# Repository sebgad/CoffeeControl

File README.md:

# CoffeeControl :coffee:

This is primarily a temperatur controller for a Rancilio Silvia Espresso machine. Parameters for controller and running the controller can be configured over a web interface. 

**default settings / no connection to wifi possible:** If no wifi is available to connect, a soft-AP (SSID: 'SilviaCoffeeCtrl', no PW)  is setup to control. It can be accessed either by the IP address of the controller or the domain http://coffee.local. In this mode plotting is currently not working (because googleCharts is used). Over the page "settings" the SSID and Password can be setup.

The project is based on an esp32 via the arduino IDE.

## code

### required aduino libaries:
- for Json handling [ArduinoJson](https://arduinojson.org/)
- for Webserver [ESPAsyncWebserver](https://github.com/me-no-dev/ESPAsyncWebServer)
- for Async TCP transfer [AsyncTCP](https://github.com/me-no-dev/AsyncTCP)

In addition there is one file required for individual setup:

"Pt1000.h" for defining individual characteristic of wheatstone bridge:
```c++
#ifndef Pt1000_h
#define Pt1000_h

#define Pt1000_CONV_SQUARE  // define for square interpolation

#include "Arduino.h"

// Define coefficients for linear regression function
// use #define Pt1000_CONV_LINEAR if you want to use the linear interpolation
// variable are only requred if this define is set
const float fPt1000LinCoeffX1 = 433.6520668;
const float fPt1000LinCoeffX0 = 82.01975366;

// Define coefficients for quadratic regression function
// use #define Pt1000_CONV_SQUARE if you want to use the square interpolation
// variable are only requred if this define is set
const float fPt1000SquareCoeffX2 = 295.16714369;
const float fPt1000SquareCoeffX1 = 417.84868016;
const float fPt1000SquareCoeffX0 = 76.91861221;

// Define lookup table for temperature calculation
// use #define Pt1000_CONV_LOOK_UP_TABLE if you want to use the lookup table
// variable are only requred if this define is set
const float arrPt1000LookUpTbl[][2] = {
                                        {-0.21396866840731069, 0.0},
                                        {-0.19826086393703643, 5.0},
                                        {-0.18283911631429636, 10.0},
                                        {-0.16770344877338753, 15.0},
                                        {-0.15282330361877822, 20.0},
                                        {-0.13821466591521075, 25.0},
                                        {-0.12386291635089636, 30.0},
                                        {-0.10976138828633408, 35.0},
                                        {-0.09589652769003139, 40.0},
                                        {-0.08227645893153232, 45.0},
                                        {-0.06888104591949339, 50.0},
                                        {-0.05571158923387528, 55.0},
                                        {-0.0427624663099406, 60.0},
                                        {-0.0300282397238783, 65.0},
                                        {-0.017503649635036495, 70.0},
                                        {-0.00518360659538545, 75.0},
                                        {0.0069431178724726535, 80.0},
                                        {0.01886859632220499, 85.0},
                                        {0.03060996495366849, 90.0},
                                        {0.04216540043842523, 95.0},
                                        {0.05353924250669009, 100.0},
                                        {0.06472982975573649, 105.0},
                                        {0.07575883980844787, 110.0},
                                        {0.08661262418699037, 115.0},
                                        {0.09730088303101485, 120.0},
                                        {0.10782733455505109, 125.0},
                                        {0.11820106425587913, 130.0},
                                        {0.12841994955774214, 135.0},
                                        {0.13848205967873975, 140.0},
                                        {0.1484014359031887, 145.0},
                                        {0.15817588158467566, 150.0},
                                        {0.16780851306788105, 155.0},
                                        {0.17730235788402426, 160.0},
                                        {0.18666535708795248, 165.0},
                                        {0.19589030865119572, 170.0},
                                        {0.20498993006709912, 175.0},
                                        {0.21395711383340363, 180.0},
                                        {0.22280417956398454, 185.0},
                                        {0.23152881217857227, 190.0},
                                        {0.2401335018563869, 195.0},
                                        {0.24862067160467974, 200.0}
                                      };
#endif
```

## PCB
- The PCB was created via KiCAD [KiCAD](https://www.kicad.org/)
- Rouing was done via the autorouter from freerouting [freerouting](https://github.com/freerouting/freerouting)
- The sorce fiels of the PCB are in *tools/PCB-KiCAD/EspressoV1*
Note:
- The autorouter cannot create a 100% working PCB but is a good start 
- Do not sace the preferenences of the outorouter. Otherweise the routing cannot be redone. See [here](https://github.com/freerouting/freerouting/issues/26#issuecomment-814837891)
- The Design uses an own libary. KiCAD might not be able to find the file initially. 
	- re-Open KiCAD: Do Fixes in "Symbol Editor" and "Footprint Editor":
	- Preferences -> Symbol Libaries|Manage Footprint Libaries : update the path of the esp32 libary
	- close and open KiCAD

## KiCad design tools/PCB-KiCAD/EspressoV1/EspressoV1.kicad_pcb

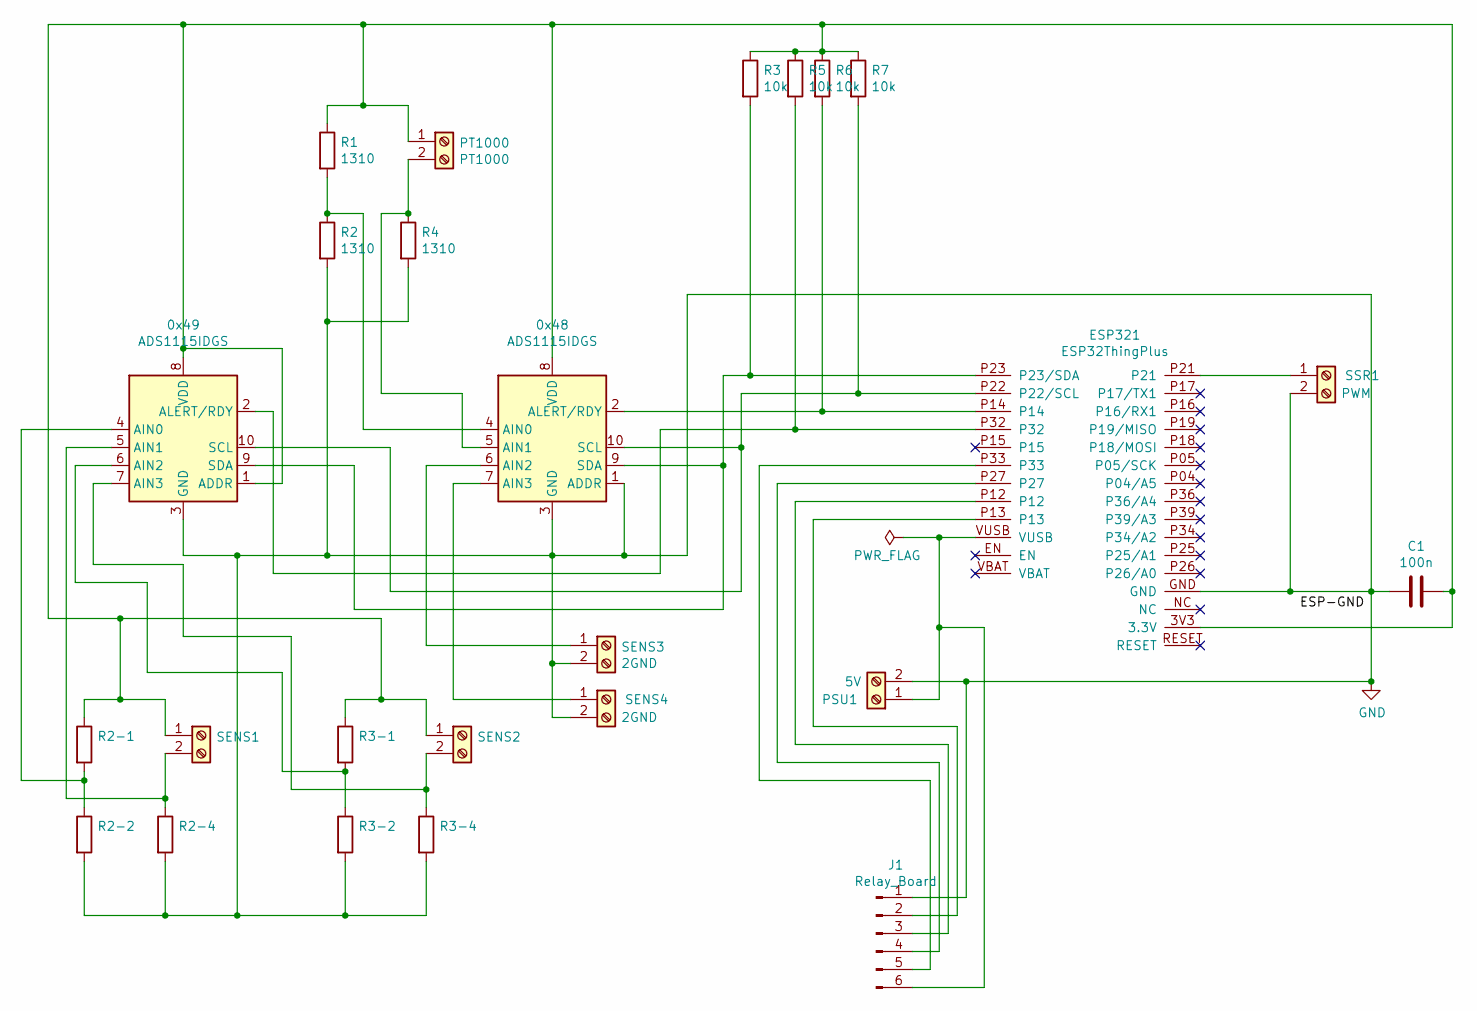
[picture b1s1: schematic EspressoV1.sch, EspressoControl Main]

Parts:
0x48, 0x49: ADS1115IDGS; ADS1115
C1: 100n; C_Rect_L13.0mm_W5.0mm_P10.00mm_FKS3_FKP3_MKS4
ESP321: ESP32ThingPlus
J1: Relay_Board; PinHeader_1x06_P2.54mm_Vertical
PSU1: 5V; TerminalBlock_Phoenix_MKDS-1,5-2-5.08_1x02_P5.08mm_Horizont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
PT1000: PT1000; TerminalBlock_Phoenix_MKDS-1,5-2-5.08_1x02_P5.08mm_Horizont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
R1, R2, R3-1, R3-2, R3-4, R4: 1310; R_Axial_DIN0207_L6.3mm_D2.5mm_P10.16mm_Horizontal
R2-1, R2-2, R2-4: 0; R_Axial_DIN0207_L6.3mm_D2.5mm_P10.16mm_Horizontal
R3, R5, R6, R7: 10k; R_Axial_DIN0207_L6.3mm_D2.5mm_P10.16mm_Horizontal
SENS1: -; TerminalBlock_Phoenix_MKDS-1,5-2-5.08_1x02_P5.08mm_Horizont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
SENS2: PT1000; TerminalBlock_Phoenix_MKDS-1,5-2-5.08_1x02_P5.08mm_Horizont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
SENS3, SENS4: 2GND; TerminalBlock_Phoenix_MKDS-1,5-2-5.08_1x02_P5.08mm_Horizont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
SSR1: PWM; TerminalBlock_Phoenix_MKDS-1,5-2-5.08_1x02_P5.08mm_Horizont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

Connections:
GND: 0x48.1 (ADDR), 0x48.3 (GND), 0x49.3 (GND), C1.2, ESP321.GND, J1.1, PSU1.2, R2.2, R2-2.2, R2-4.2, R3-2.2, R3-4.2, R4.2, SENS3.2, SENS4.2, SSR1.2
unnamed: 0x48.2 (ALERT/RDY), ESP321.P14, R6.2
unnamed: 0x48.4 (AIN0), R1.2, R2.1
unnamed: 0x48.5 (AIN1), PT1000.2, R4.1
unnamed: 0x48.6 (AIN2), SENS3.1
unnamed: 0x48.7 (AIN3), SENS4.1
unnamed: 0x48.8 (VDD), 0x49.1 (ADDR), 0x49.8 (VDD), C1.1, ESP321.3V3 (3.3V), PT1000.1, R1.1, R2-1.1, R3.1, R3-1.1, R5.1, R6.1, R7.1, SENS1.1, SENS2.1
unnamed: 0x48.9 (SDA), 0x49.9 (SDA), ESP321.P23 (P23/SDA), R3.2
unnamed: 0x48.10 (SCL), 0x49.10 (SCL), ESP321.P22 (P22/SCL), R7.2
unnamed: 0x49.2 (ALERT/RDY), ESP321.P32, R5.2
unnamed: 0x49.4 (AIN0), R2-1.2, R2-2.1
unnamed: 0x49.5 (AIN1), R2-4.1, SENS1.2
unnamed: 0x49.6 (AIN2), R3-1.2, R3-2.1
unnamed: 0x49.7 (AIN3), R3-4.1, SENS2.2
unnamed: ESP321.P12, J1.3
unnamed: ESP321.P13, J1.2
unnamed: ESP321.P21, SSR1.1
unnamed: ESP321.P27, J1.4
unnamed: ESP321.P33, J1.5
unnamed: ESP321.VUSB, J1.6, PSU1.1

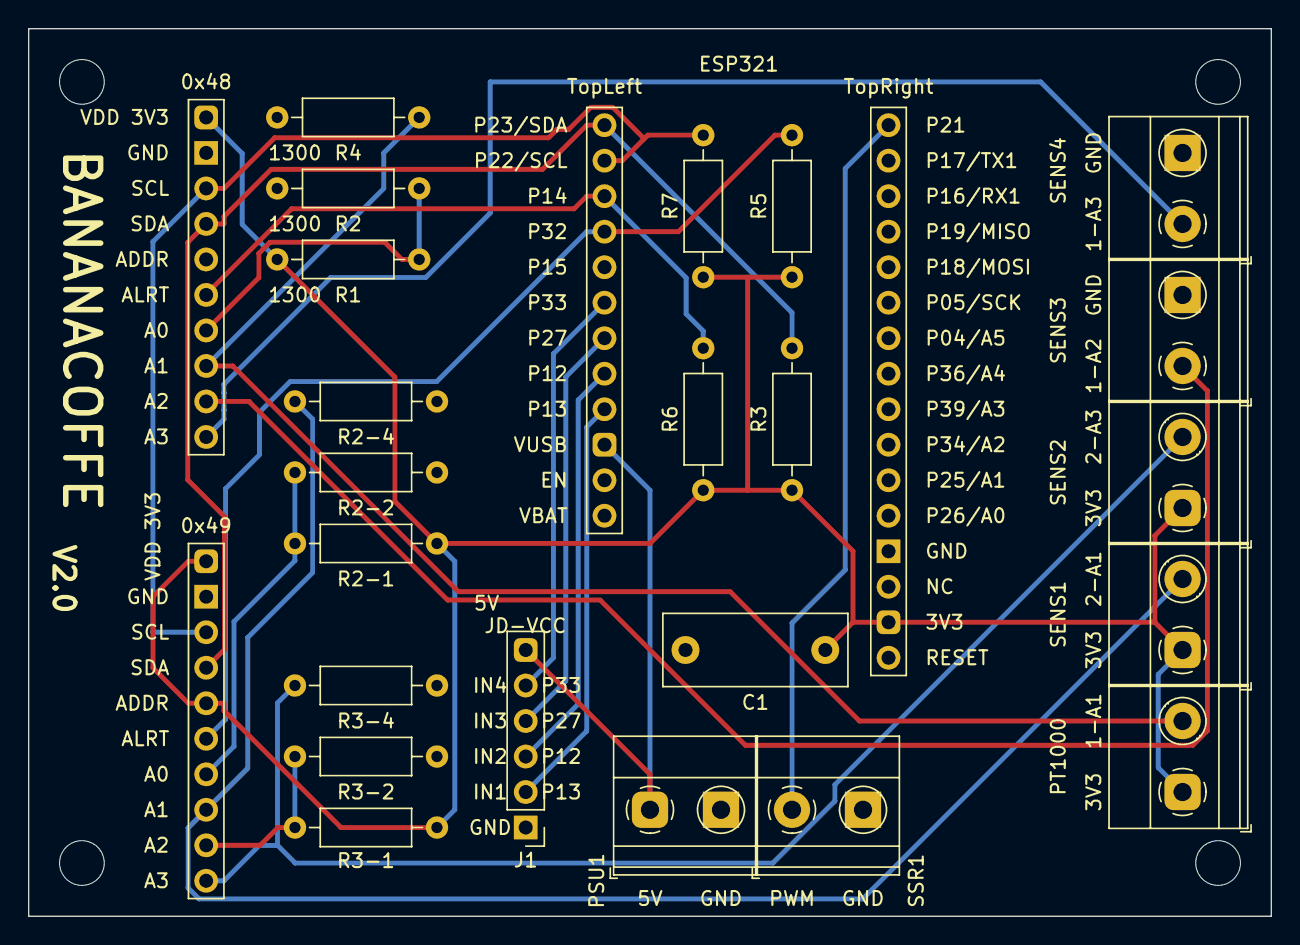
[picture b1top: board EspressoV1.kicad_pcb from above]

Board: 2 copper layers, 88.9 x 63.5 mm, 29 parts (0 on the bottom side), 20 nets.

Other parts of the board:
OL: MountingHole_3.2mm_M3
OR: MountingHole_3.2mm_M3
UL: MountingHole_3.2mm_M3
UR: MountingHole_3.2mm_M3

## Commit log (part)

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2021-04-24 inital create
2021-04-24 add .vscode to gitignore
2021-04-25 add wifi connection function
2021-04-25 add mDNS service
2021-04-25 Delete index.html
    delete because license is unknown
2021-04-25 add TODOs
2021-04-29 add timer and ISR based on https://techtutorialsx.com/2017/10/07/esp32-arduino-timer-interrupts/
2021-05-02 add index.html
2021-05-02 change layout of index.html
2021-05-08 divide stylesheet and java script for status table. add google graph
2021-05-08 start Json data handling
2021-05-09 add TODOs, have fun :-)
2021-05-12 Dont look at me. This is just an ugly debugg nano sketch for testing the SSR. This code is verry ugly.
2021-05-13 used pin 6 as slow "pwm"like and pin 3 as normal pwm
2021-05-13 naming mistake
2021-05-13 added shortcut to gitignore so i dont stage by mistake
2021-05-13 correct pwm usage
2021-05-15 add JSON generator, dummy output for debugging
2021-05-16 Add python file to calculate maximum signal measurement
2021-05-17 start implementing csv file
2021-05-22 add three timers, still bugfixing timer 3 (measurement stream)
2021-05-22 fixed timer3 issue
2021-05-24 sensor read out, pid control and measurement write depend now on one timer
2021-05-30 change timer settings, implement status variables, minor changes on setup
2021-05-30 added description to the readme
2021-05-30 start implementing ADS1115
2021-05-31 extend function getPolarity() and setPolarity()
2021-05-31 link fix for README.md
2021-05-31 added link and setup for online tool to simulate wheatstone bridge
2021-06-02 change bit shifting functionality and add missing register settings
2021-06-03 implement pinready mode
2021-06-03 add missing functionalities, add comments
2021-06-04 change bit significance conversion and add initial setup of ADS1115
2021-06-04 add physical conversion method
2021-06-10 setup temp sensor
2021-06-12 initial iteration of PCB. PCB created with KiCAD.
2021-06-12 added info about the PCB
2021-06-13 PT1000 lookup table; with 7 support points
2021-06-14 add physical conversion table, fix integer problem
2021-06-14 bugfix i2c func
2021-06-15 fix bitread and write in ADS1115 lib
2021-06-16 fix bitwrite()
2021-06-17 fix issue in writeBit and rename function
2021-06-18 change implementation from set- and read_physical in ADS1115 lib
2021-06-19 adapt calculation for Resistor R1,R2,R4 from 1310Ohm to 1298Ohm
2021-06-20 implement csv parsing in webserver to read out actual sensor values
2021-06-20 added PID and some comments
2021-06-21 added 1310 ohm calibration; fixt Pin typo
2021-06-21 1310 ohm setup
2021-06-26 change time column in measurement file
2021-06-26 define PT1000 conversion table in separate header file
2021-06-26 implement regression square function for readPhysical()
2021-06-26 get interpolation values for .h file
2021-06-26 read voltage in V
2021-06-27 adapt physical conversion set
2021-06-29 connect line chart with data.csv
2021-06-29 change pwm chart
2021-07-11 comment graphs.html, add another status indicator, but not finished
2021-07-14 cleanup main script, change register readout functionality in ADS1115 and change layout of graphs.html including css file
2021-08-21 minor changes
2021-08-27 add pid parameter handling
2021-08-27 implement ArduinoJson for parameter handling
2021-09-01 add JsonLib
2021-09-06 add comments
2021-09-10 adapted PID lib: fixed controller calculation; other coefficients; added OnOffThresholds
2021-09-10 implement parameter update
2021-09-10 clean up graphs.html
2021-09-11 finished Parameter setup
2021-09-12 extend online calibrations and functionality to up and download file
2021-09-12 added method to only add off or on threshold + spelling
2021-09-14 split setup function, bugfix graphs.html
2021-09-18 only use On threshold
2021-09-18 fist commissioning of temp controller. tuning parameters need to be adapted.
2021-09-18 updated tuning parameters
2021-09-20 added TODO so I dont forget
2021-09-26 add access protection for parameter file and measfile
2021-10-03 clean up web interface, add memory allocation to measurement file
2021-10-03 PCB V2
2021-10-03 correct resistor value
2021-10-10 add wifi signal strength information
2021-10-29 add softAP if wifi connection is not possible. Wifi settings now stored in json-file
2021-10-29 update wifi soft ap description
2021-11-01 remove include to WifiAccess.h file, bugfixes
2021-11-01 implement reconnect event on disconnect from wifi
2021-12-23 change pid controler, add ota functionality
2021-12-23 change coefficient names of PID controller, implement time factor switch for coefficients
2021-12-27 add raw measurement data
2021-12-28 clarify controller parameters
2021-12-28 added RGB LED for pin 13, 12 and 27 and on off pid
2021-12-29 LED write call every 2.5s for debouncing. Change orange to purple
2021-12-30 add json request lastValues, update index.html and graphs.html
2021-12-30 wifi SSID/PW is not default gotten from h-file
2021-12-30 add antiwindup, add control parameter ods file
2021-12-31 increase sensitivity of ADS1115 to +-0.256V, minor changes
2022-01-01 add conversion monitoring if sensor values are freezing, minor changes
2022-01-01 bugfix sensor diagnosis
2022-01-01 temporary disable diagnosis function. Need to analyze bug.
2022-01-03 remove diagnosis for now, because sum up the delta is not sufficient for identifying malfunction of ADS1115
2022-01-04 default python script; added to git ignore
2022-01-04 got orange and yellow working
    changes HW ins of Gereen and blue
2022-01-04 added tool to calc md5 for win10
2022-01-04 tool can now correctly been rerun
2022-01-04 added missing config parameters and made them changeable
2022-01-04 start reorganizing JSON, add menu.js for generating navbar
2022-01-05 add json structure and start changing http server
2022-01-06 change JSON structure and settings, remove channels from settings, led color change
2022-01-07 added 8-point mean filter option in getVoltVal
    default is no filter (off)
    filter is off
2022-01-07 implement signal filter, changed setup call order, minor fixes in pyhton scripts
2022-01-07 optimize settings.html page
2022-01-08 add savitzgy golay filter
2022-01-14 remove variable buffer size, add savitzky golay filter for odd buffer size
2022-01-15 change settings button layout
2022-01-16 adapt RGB LED brightness
2022-01-16 activating filter; but stopping implementation for now
2022-01-16 measurement of step response and py file to plot
2022-01-16 added diagnosis for when the sensor is stuck and had 10 times the same value
2022-01-16 adapt LED setColor()
2022-01-16 bugfix error LED status
2022-01-19 bugfix diagnosis function
2022-01-19 bugfix LED issue
2022-01-21 implement hardware watchdog functionality
2022-01-22 rework of diagnosis; not use min==max anymore but check for changed values
    rename of misleading variable name
2022-01-22 bugfix initializing buffer in ADS1115.cpp, updating all *.html, minor bugfixes, optimize webserver
2022-01-22 bugfix merge conflict :-)
2022-01-22 add gain factor for each color, e.g. orange, purple, etc.
2022-01-22 bugfix esp restart request over webserver, adapt JSON document size
2022-01-23 added favicon and renamed to BananaCoffee
2022-01-23 redirect fix when uploading files
2022-01-23 added missing import -> merge error fix
2022-01-23 temporary bugfix interrrupt call
2022-01-24 bugfix filter settings, setting filter size to 11, comment fileblock method to check repsonsiveness of webserver
2022-01-29 add ADS1015, state change state machine to implement oversampling in onAlertRdy()
2022-01-30 change to core v2 and littleFS
2022-01-30 bugfix
2022-02-04 change i2c in ads1015
2022-02-05 bugfix ADS1015 assignment
2022-02-06 fix i2c timing issue
2022-02-07 add ota.h and failsafe request
2022-02-08 change to ADS1115
2022-02-08 change filter size
2022-02-08 added favicons for littleFS
2022-02-13 combine all csv to one combined csv
2022-02-13 model for simulating step response
2022-02-19 add curve fit pyhton file
2022-02-27 show WiFi strength in index.html; better filtering and filter debugging.
2022-02-27 bugfix buffer print, change readOut WifiSignal
2022-03-03 cleanup and read the register without changing the filter buffer at the end of setup()
2022-03-05 change index.html layout
2022-03-05 fix first conversion
2022-03-15 start redirecting log output to logfile, add conversion mode diagnosis
2022-03-16 implement log rotation, add log.html to watch debug log
2022-03-16 bugfix diagnosis loop ESP_OK
2022-03-27 increase watchdog timeout, to cover time at reset. turn led to purple when ADS needs to be reconfigured
2022-12-26 add standby timeout
2023-06-04 fixed missing semicolon
2023-06-04 change timeout in i2c, operating range
2023-06-04 set default timeout to 1h
2023-06-08 removed false -positive detection of frozen value for temperatures below 35°C
2023-06-11 added log to timeout, high threshold and updated default values
2023-06-24 bugfix LED-Ctrl, extend timeout in I2C communication
2023-06-24 add wifi-reconnect() and remove wifi.connect() in mainloop
2023-06-24 bugfix iState check
2023-06-24 add wifi reconnect, change i2c clock speed, bugfix diagnosis
2023-09-19 disable ADS sensor freeze, add button to deactivate PID#
2023-11-19 added logos
2023-11-19 PID controller can now sleep
2023-11-19 clean up loop and use sleep mode
2023-11-19 wake up method (not used yet)
2023-11-19 method to reset the PID
2023-11-19 prepare dynamic sleep timer
2024-03-29 add serial print output also to UART
2024-04-21 deactivate diagnosis reaction
2024-05-18 Add logic for brew detection
2024-05-18 add build folder to gitignore
2024-05-18 change comment style
2024-05-18 add brewing to measurement
2024-05-18 change GPIO Number
2024-05-20 add PID object for brewing activated
2024-05-20 add debouncing time
2024-05-21 add separat file for data types and defines
2024-06-02 add target temperature to chart, optimize isr for brew detection
2024-07-21 add reset function in PID controller, add struct for status
